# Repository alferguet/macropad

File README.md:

# Simple mechanical macropad

Mechanical macropad created for learning with the Ai03 guide.

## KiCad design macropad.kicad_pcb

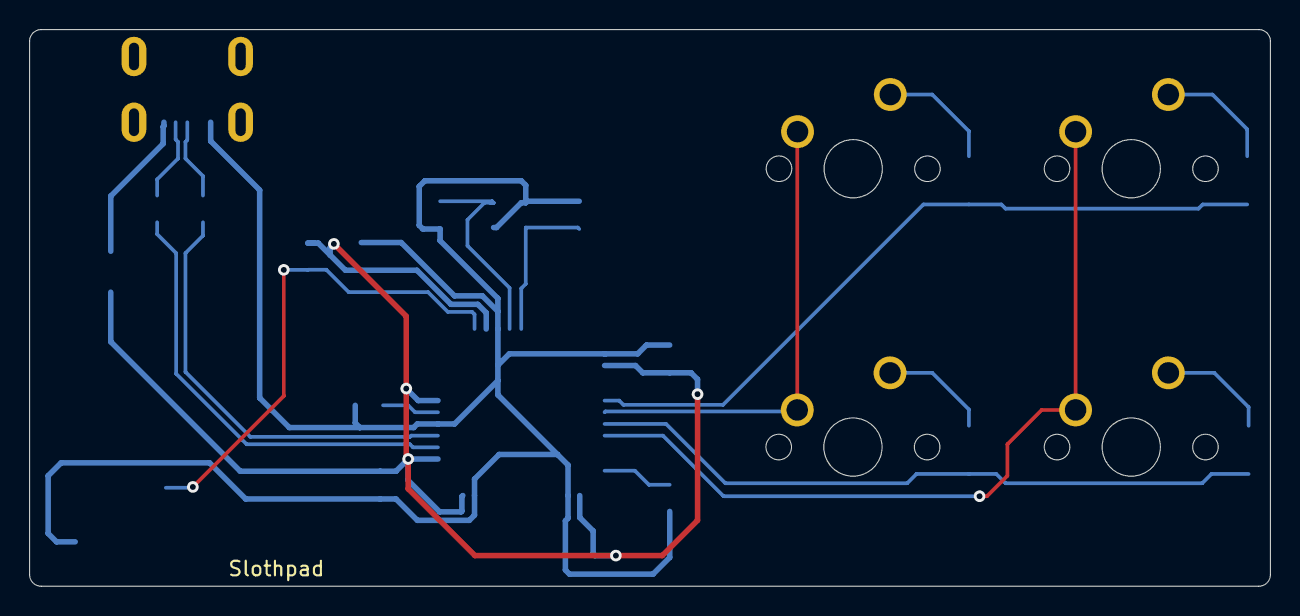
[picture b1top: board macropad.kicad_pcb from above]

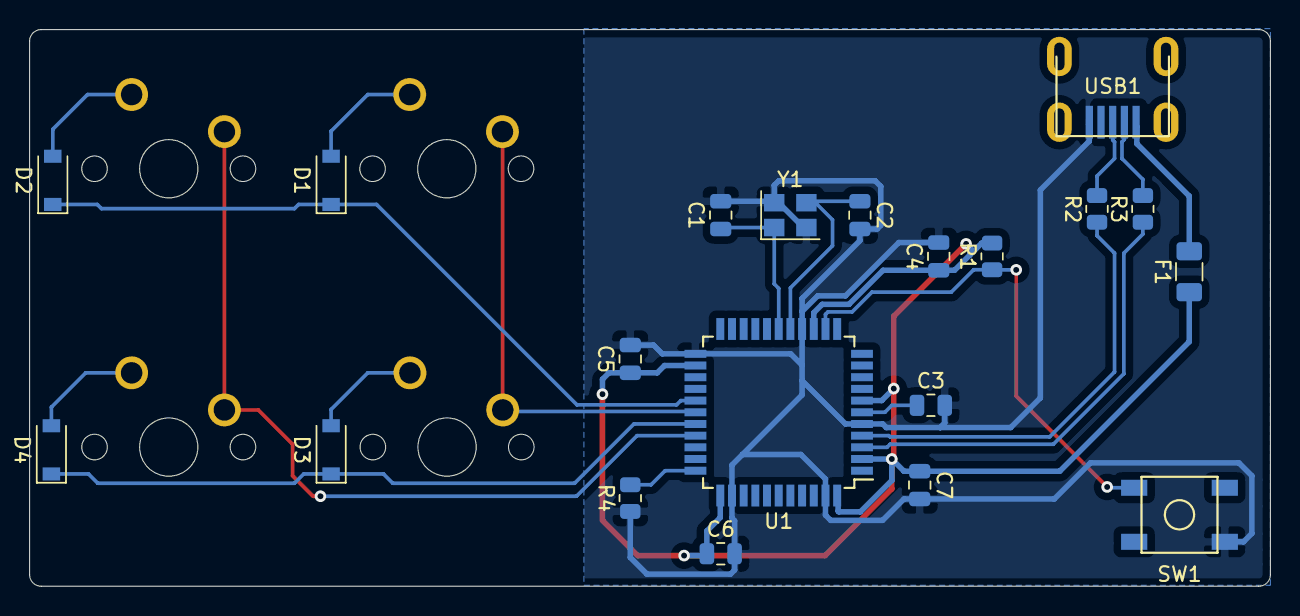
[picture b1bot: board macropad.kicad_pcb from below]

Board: 2 copper layers, 84.9 x 38.1 mm, 24 parts (20 on the bottom side), 20 nets.

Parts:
C1, C2: 22pF; C_0805_2012Metric
C3: 1uF; C_0805_2012Metric
C4, C5, C6: 0.1uF; C_0805_2012Metric
C7: 10uF; C_0805_2012Metric
D1, D2, D3, D4: SOD_123; D_SOD-123
F1: 50mA; Fuse_1206_3216Metric
MX1, MX2, MX3, MX4: MX-NoLED; MXOnly-1U-NoLED
R1, R4: 10k; R_0805_2012Metric
R2, R3: 22; R_0805_2012Metric
SW1: SW_Push; SKQG-1155865
U1: ATmega32U4-AU; TQFP-44_10x10mm_P0.8mm
USB1: Molex-0548190589
Y1: 16MHz; Crystal_SMD_3225-4Pin_3.2x2.5mm

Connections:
+5V: C4.1, C5.1, C6.1, C7.1, F1.1, R1.2, U1.2, U1.7, U1.14, U1.24, U1.34, U1.44
COL0: MX1.1, MX3.1, U1.28
COL1: MX2.1, MX4.1, U1.30
D+: R2.2, USB1.3
D-: R3.2, USB1.4
GND: C1.2, C2.2, C3.2, C4.2, C5.2, C6.2, C7.2, R4.1, SW1.1, U1.5, U1.15, U1.23, U1.35, U1.43, USB1.1, Y1.2, Y1.4
unnamed: C1.1, U1.17, Y1.1
unnamed: C2.1, U1.16, Y1.3
unnamed: C3.1, U1.6
unnamed: D1.2, MX1.2
unnamed: D2.2, MX2.2
unnamed: D3.2, MX3.2
unnamed: D4.2, MX4.2
unnamed: R1.1, SW1.2, U1.13
unnamed: R2.1, U1.4
unnamed: R3.1, U1.3
unnamed: R4.2, U1.33
ROW0: D1.1, D2.1, U1.27
ROW1: D3.1, D4.1, U1.29
VCC: F1.2, USB1.5

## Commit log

2020-12-07 add README
2020-12-07 Submodules and init project
2020-12-22 Finished schematics
2020-12-22 placed components
2020-12-23 Completed macropad
